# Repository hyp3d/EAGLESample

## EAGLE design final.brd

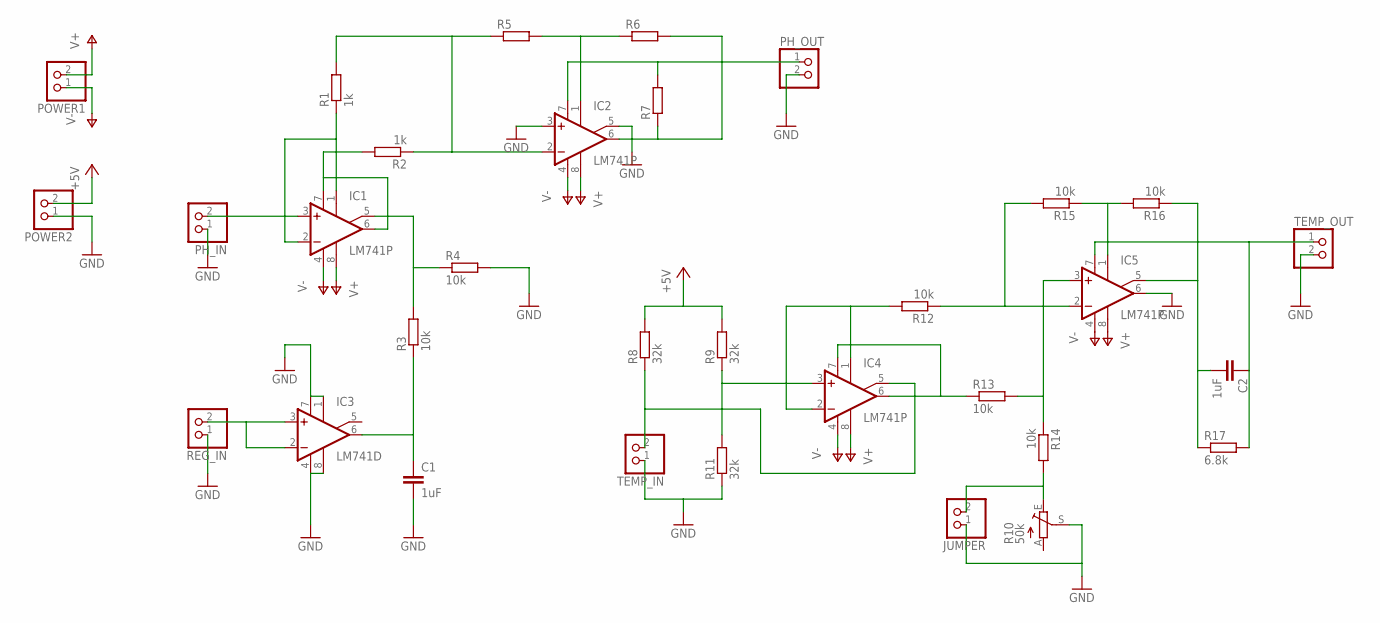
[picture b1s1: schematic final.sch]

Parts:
C1, C2: 1uF; C0805K
IC1, IC2, IC4, IC5: LM741P; DIL08
IC3: LM741D; SO08
JUMPER: PINHD-1X2; 1X02
PH_IN: PINHD-1X2; 1X02
PH_OUT: PINHD-1X2; 1X02
POWER1, POWER2: PINHD-1X2; 1X02
R1, R2: 1k; R0805
R3, R4, R12, R13, R14, R15, R16: 10k; R0805
R5, R6, R7: R-EU_R0805; R0805
R8, R9, R11: 32k; R0805
R10: 50k; S64W
R17: 6.8k; R0805
REG_IN: PINHD-1X2; 1X02
TEMP_IN: PINHD-1X2; 1X02
TEMP_OUT: PINHD-1X2; 1X02

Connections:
+5V: POWER2.2, R8.2, R9.2
GND: C1.2, IC2.3 (+IN), IC2.5 (ON2), IC3.1 (ON1), IC3.4 (V-), IC3.7 (V+), IC3.8 (OPT), IC5.6 (OUT), JUMPER.1, PH_IN.1, PH_OUT.2, POWER2.1, R4.2, R10.S, R11.1, REG_IN.1, TEMP_IN.1, TEMP_OUT.2
unnamed: IC1.1 (ON1), IC1.2 (-IN), R1.1
unnamed: IC1.3 (+IN), PH_IN.2
unnamed: IC2.2 (-IN), R1.2, R2.1, R5.1
unnamed: IC1.6 (OUT), IC1.7 (V+), R2.2
unnamed: IC3.2 (-IN), IC3.3 (+IN), REG_IN.2
unnamed: IC1.5 (ON2), R3.2, R4.1
unnamed: IC2.1 (ON1), R5.2, R6.1
unnamed: C1.1, IC3.6 (OUT), R3.1
unnamed: IC2.6 (OUT), R6.2, R7.1
unnamed: IC2.7 (V+), PH_OUT.1, R7.2
unnamed: IC4.5 (ON2), R8.1, TEMP_IN.2
unnamed: IC4.3 (+IN), R9.1, R11.2
unnamed: IC5.1 (ON1), R15.1, R16.2
unnamed: JUMPER.2, R10.E, R14.2
unnamed: C2.1, IC5.7 (V+), R17.2, TEMP_OUT.1
unnamed: IC4.1 (ON1), IC4.2 (-IN), R12.2
unnamed: IC4.6 (OUT), IC4.7 (V+), R13.1
unnamed: C2.2, IC5.5 (ON2), R16.1, R17.1
unnamed: IC5.3 (+IN), R13.2, R14.1
unnamed: IC5.2 (-IN), R12.1, R15.2
V+: IC1.8 (OPT), IC2.8 (OPT), IC4.8 (OPT), IC5.8 (OPT), POWER1.2
V-: IC1.4 (V-), IC2.4 (V-), IC4.4 (V-), IC5.4 (V-), POWER1.1

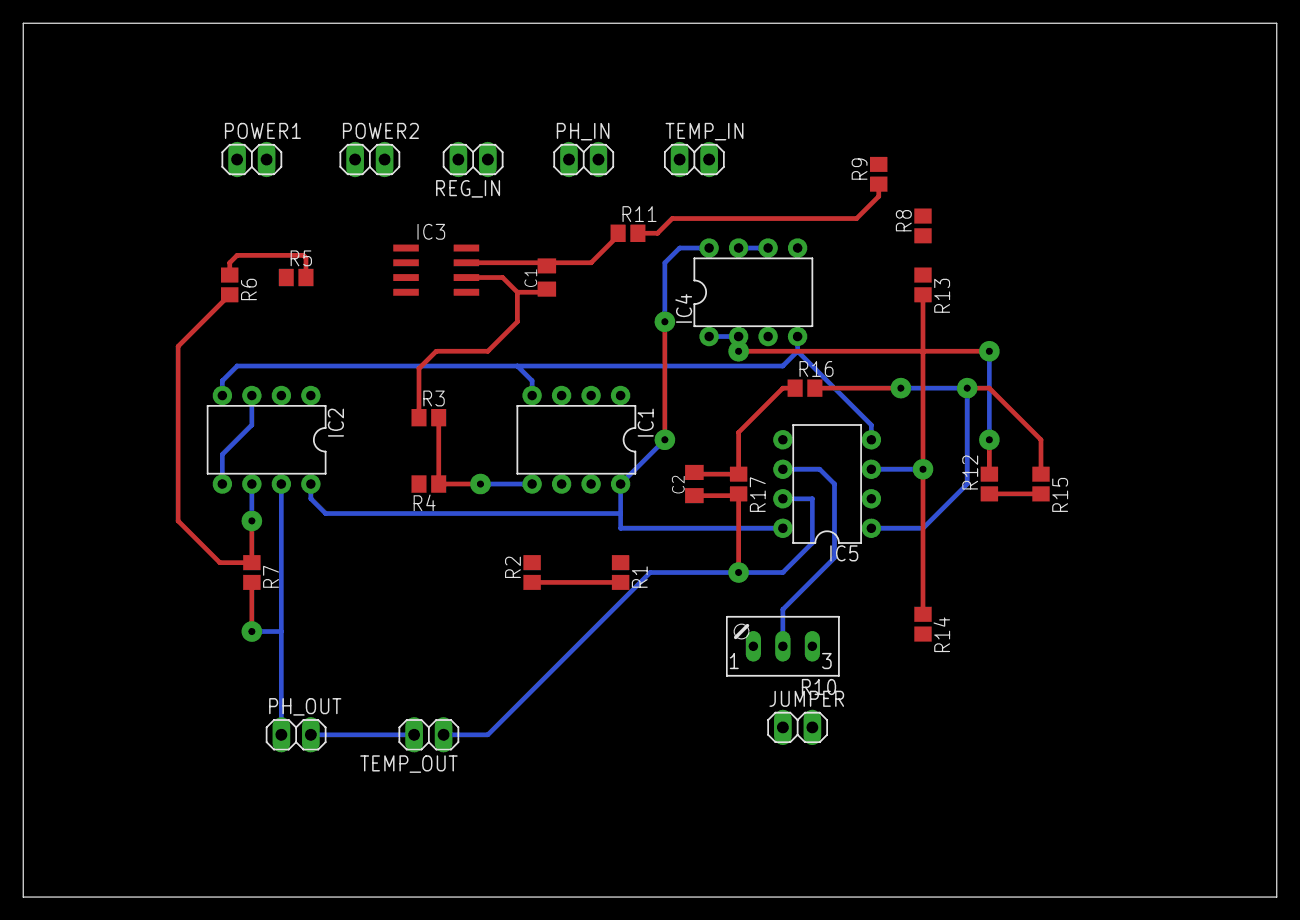
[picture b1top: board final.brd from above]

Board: 2 copper layers, 107.9 x 75.2 mm, 32 parts (0 on the bottom side), 24 nets.

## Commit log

2017-09-27 choHo_2
2017-09-27 master_2
